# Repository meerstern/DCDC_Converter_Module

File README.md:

# DCDC_Converter_Module
Non-insulated boost type DCDC Converter Module with ADP1612 (1.8~5.5V -> +15/-15V)

## 概要 
  * [ADP1612スイッチングコンバータ][1]を使用した昇圧電源です
  * 1.8V~5.5Vの入力で±15.1Vの出力が得られます
  * スイッチング周波数が1.3MHzと高いため、AD変換用電源やオーディオ向け電源に最適です
  * [シングル出力のスイッチングコンバータで両電源を得る(PDF,P.21電源回路参照)][2]ことでコンバータICコストの削減が可能です
  * 出力はR2,R5で決定され、デフォルトは±15.1Vで固定されています
  * 出力有効ENは内部プルアップされているため、未接続orVIN接続で出力ONします
  * それぞれ最大200mA程度の出力を得られます  
  * サイズ40mm x30mm、M3x2、間隔22mm  
  * Ni-MH電池2本2.4V電源供給、負荷100ｍAの場合、Peak-Peakで30~50mV前後、RMSで30mV前後のリップルです
    ※負荷や測定条件によって異なるため、性能を保証するものではありません  

## 注意
  * ±15Vで両側に同じような負荷を接続してください
  * +15V側のみを電圧フィードバックする回路のため、負荷のアンバランスで出力電圧が不安定になる場合があります  
  * リップルを更に低減させるためには必要に応じて負荷側にコンデンサやフィルタを実装してください  

[1]: https://www.analog.com/jp/products/adp1612.html
[2]: https://www.analog.com/media/en/technical-documentation/data-sheets/ADAS3023.pdf

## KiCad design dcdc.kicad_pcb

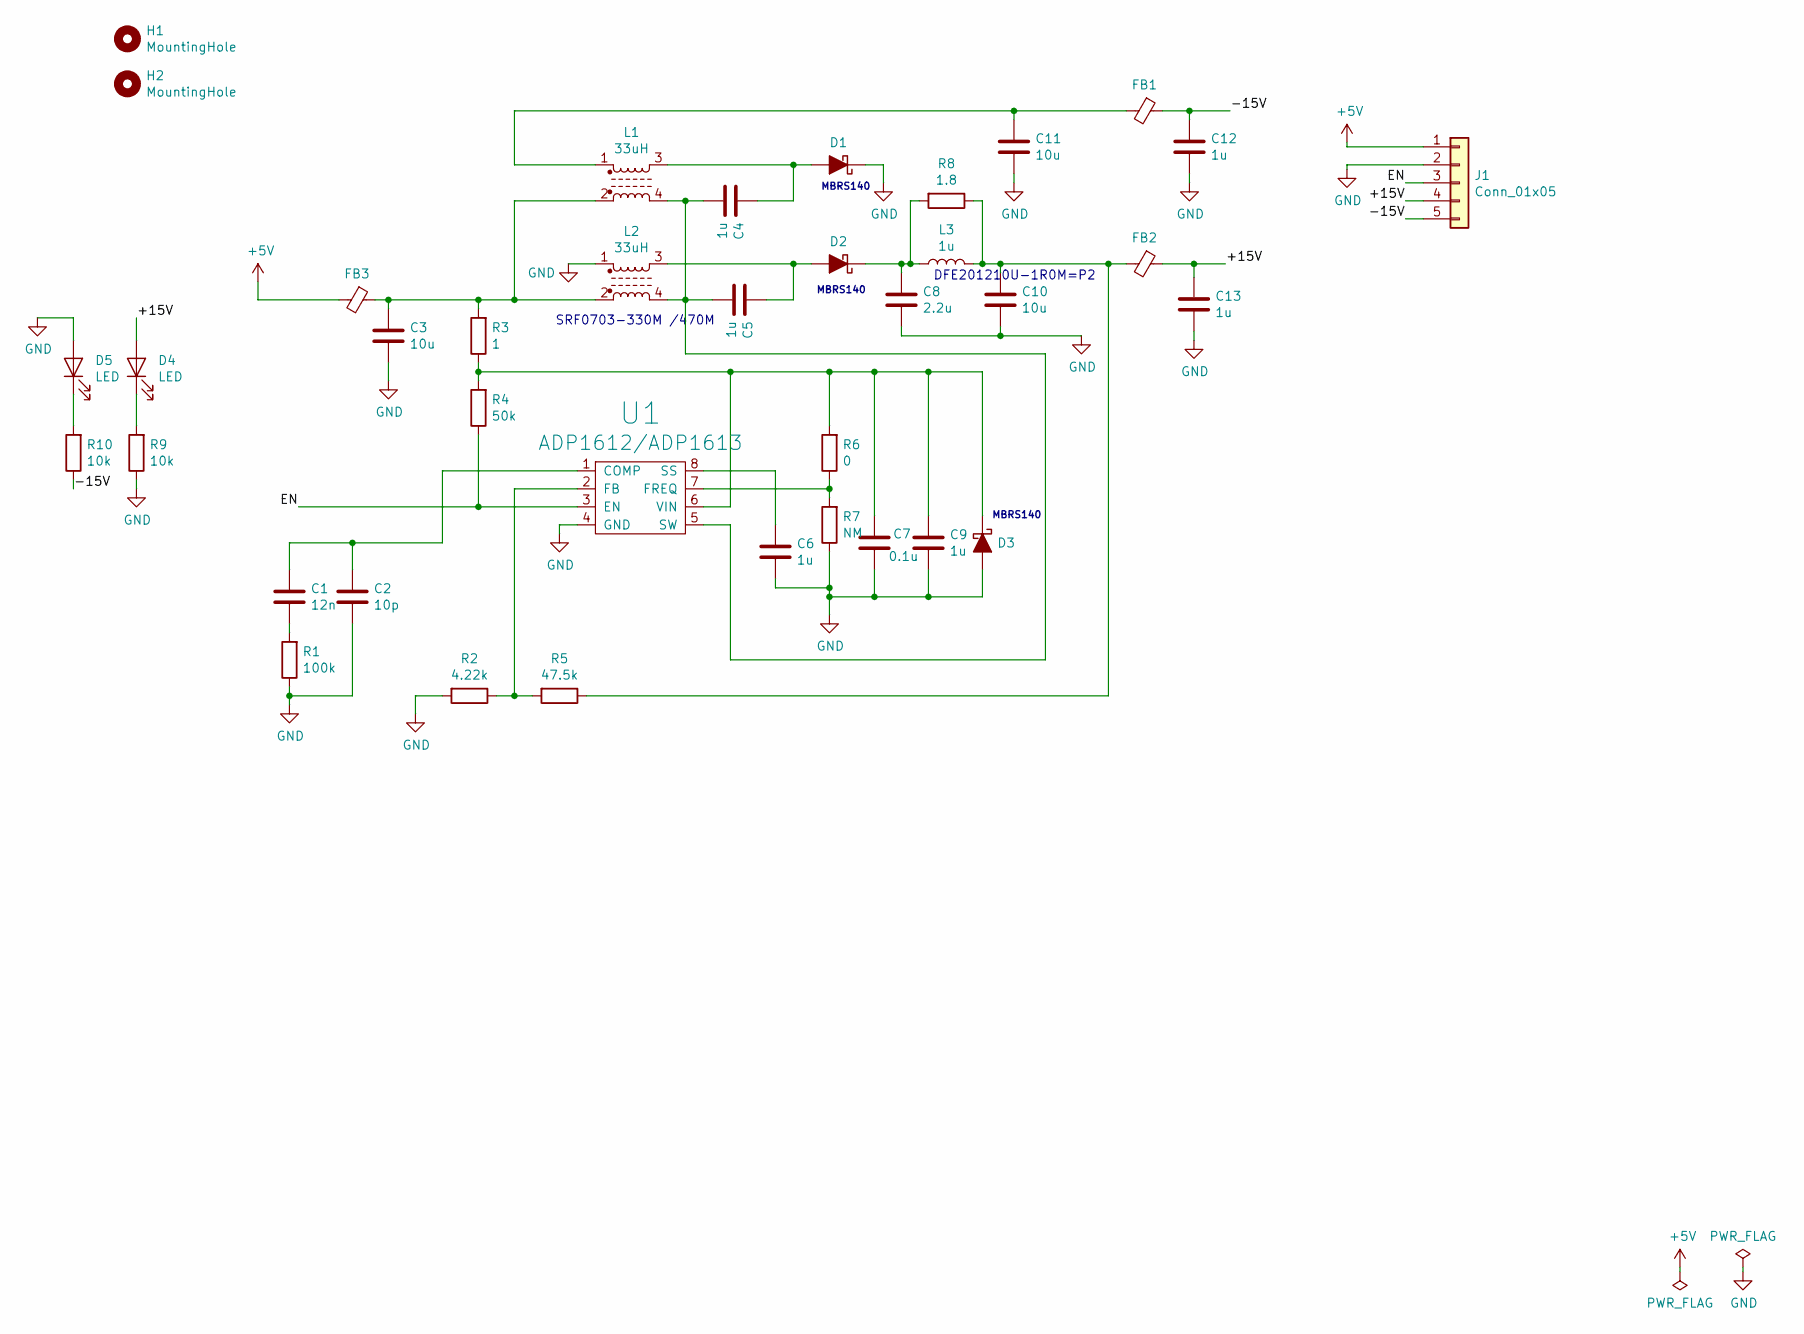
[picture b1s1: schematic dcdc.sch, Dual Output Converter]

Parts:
C1: 12n; C_0603_1608Metric
C2: 10p; C_0603_1608Metric
C3, C10, C11: 10u; C_0805_2012Metric
C4, C5, C6, C9, C12, C13: 1u; C_0603_1608Metric
C7: 0.1u; C_0603_1608Metric
C8: 2.2u; C_0603_1608Metric
D1, D2, D3: D_Schottky_ALT; D_SMB
D4, D5: LED; D_0603_1608Metric
FB1, FB2, FB3: Ferrite_Bead_Small; L_0805_2012Metric
H1, H2: MountingHole; MountingHole_3.2mm_M3
J1: Conn_01x05; PinHeader_1x05_P2.54mm_Vertical
L1, L2: 33uH; SRF0703
L3: 1u; L_0805_2012Metric
R1: 100k; R_0603_1608Metric
R2: 4.22k; R_0603_1608Metric
R3: 1; R_0603_1608Metric
R4: 50k; R_0603_1608Metric
R5: 47.5k; R_0603_1608Metric
R6: 0; R_0603_1608Metric
R7: NM; R_0603_1608Metric
R8: 1.8; R_0603_1608Metric
R9, R10: 10k; R_0603_1608Metric
U1: ADP1612/ADP1613; MSOP-8_3x3mm_P0.65mm

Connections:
+5V: FB3.2, J1.1
/+15V: C13.1, D4.2 (A), FB2.1, J1.4
/-15V: C12.1, FB1.1, J1.5, R10.1
/EN: J1.3, R4.1, U1.3 (EN)
GND: C2.2, C3.2, C6.2, C7.2, C8.2, C9.2, C10.2, C11.2, C12.2, C13.2, D1.1 (K), D3.2 (A), D5.2 (A), J1.2, L2.1, R1.1, R2.2, R7.1, R9.1, U1.4 (GND)
unnamed: C1.1, C2.1, U1.1 (COMP)
unnamed: C1.2, R1.2
unnamed: C3.1, FB3.1, L1.2, L2.2, R3.2
unnamed: C4.1, D1.2 (A), L1.3
unnamed: C4.2, C5.2, L1.4, L2.4, U1.5 (SW)
unnamed: C5.1, D2.2 (A), L2.3
unnamed: C6.1, U1.8 (SS)
unnamed: C7.1, C9.1, D3.1 (K), R3.1, R4.2, R6.2, U1.6 (VIN)
unnamed: C8.1, D2.1 (K), L3.1, R8.2
unnamed: C10.1, FB2.2, L3.2, R5.1, R8.1
unnamed: C11.1, FB1.2, L1.1
unnamed: D4.1 (K), R9.2
unnamed: D5.1 (K), R10.2
unnamed: R2.1, R5.2, U1.2 (FB)
unnamed: R6.1, R7.2, U1.7 (FREQ)

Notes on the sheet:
MBRS140
SRF0703-330M /470M
DFE201210U-1R0M=P2

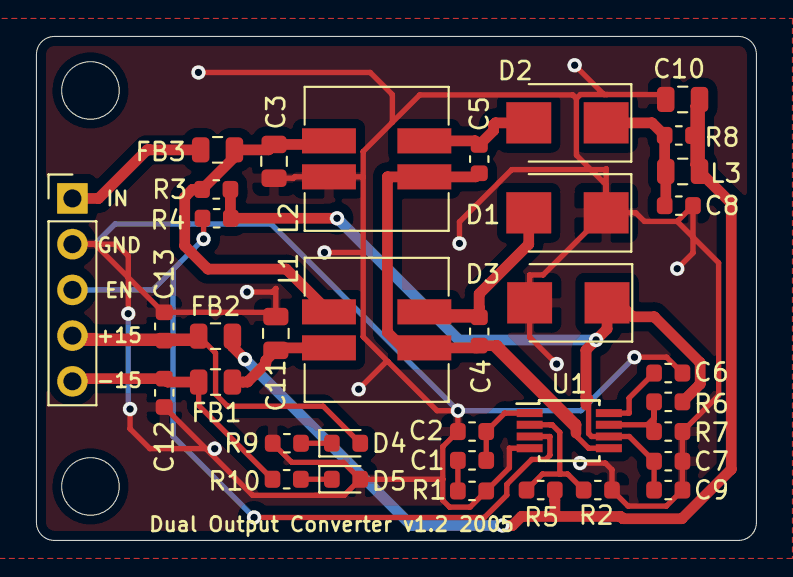
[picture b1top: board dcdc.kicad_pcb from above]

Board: 2 copper layers, 40.0 x 28.0 mm, 38 parts (0 on the bottom side), 20 nets.

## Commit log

2020-05-07 Add files as Release version
2020-05-07 Add README
2020-06-14 Add Ripple
2020-06-15 Add images
